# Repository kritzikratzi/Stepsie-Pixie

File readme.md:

<font color="red">WIP, please come back in a few weeks/months</font>

# Stepsie Pixie (WIP!)

This is a small project that combines: 

* stepper motor (to move your camera)
* relais (to trigger virtually any SLR camera)
* display+buttons (to adjust a few settings in place)
* esp8266 (as a controller, if things go well it'll also offer a web-ui)

The repository contains the code for the Arduino IDE and (soon) the eagle layout for making the board.

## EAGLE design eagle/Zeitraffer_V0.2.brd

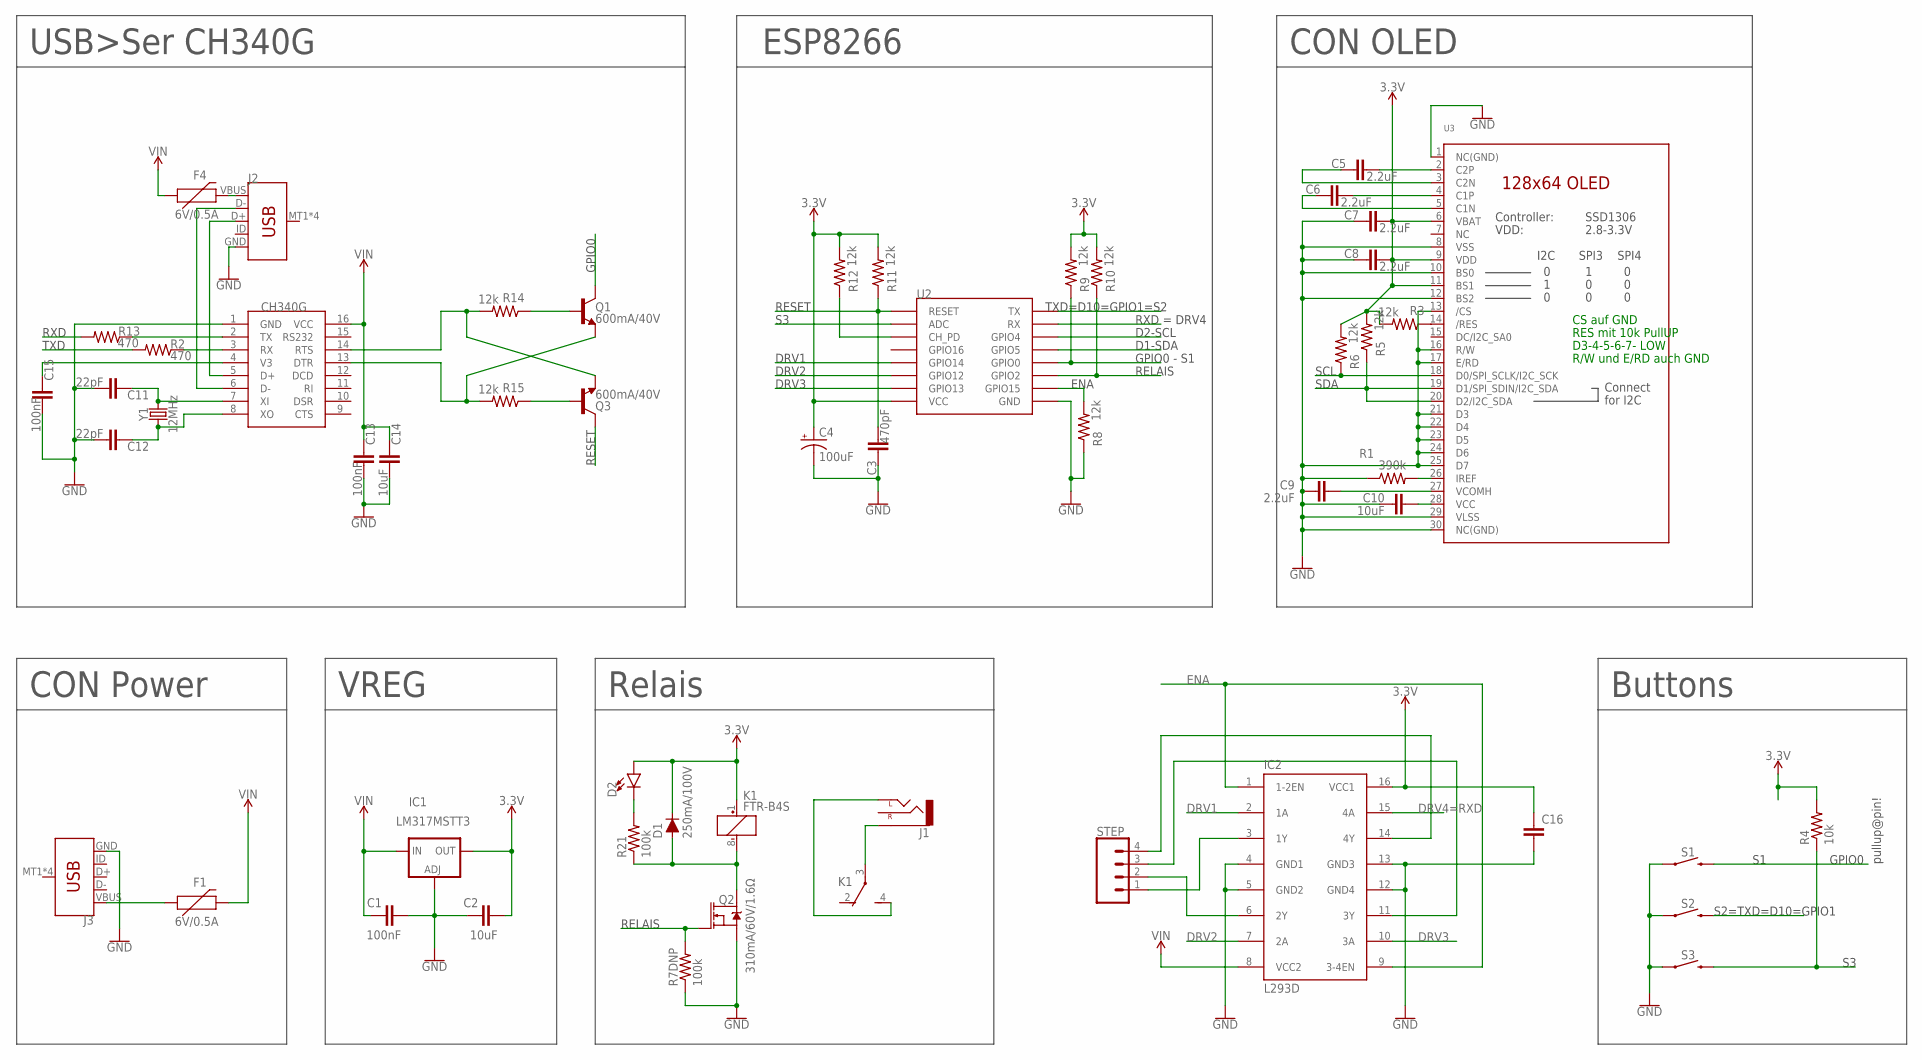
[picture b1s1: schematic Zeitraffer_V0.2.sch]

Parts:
C1, C13, C15: 100nF; 0805
C2, C10, C14: 10uF; 0805
C3: 470pF; 0805
C4: 100uF; EIA7343
C5, C6, C7, C8, C9: 2.2uF; 0805
C11, C12: 22pF; 0805
C16: C-EUC0805; C0805
D1: 250mA/100V; SOD-323
D2: LED1206-BOTTOM; LED-1206-BOTTOM
F1, F4: 6V/0.5A; 1206
IC1: LM317MSTT3; SOT223
IC2: L293D; DIL16
J1: AUDIO_JACK_2.5MM_2.5MM; STEREOJACK2.5MM_STEREOJACK2.5MM
J2, J3: USB_MICRO-B_SMT; USB-MICROB
K1: FTR-B4S
Q1, Q3: 600mA/40V; SOT23-3
Q2: 310mA/60V/1.6Ω; SOT323
R1: 390k; 0805
R2, R13: 470; 0603
R3, R5, R6, R8, R9, R10, R11, R12, R14, R15: 12k; R0805
R4: 10k; R0805
R7DNP, R21: 100k; R0805
S1, S2, S3: MOMENTARY-SWITCH-SPST-PTH-6.0MM; TACTILE_SWITCH_PTH_6.0MM
STEP: CONN_04JST-PTH; JST-4-PTH
U2: ESP12SMD; ESP12-SMD
U3: DISP_OLED_UG-2864HSWEG01; UG-2864HSWEG01_1.3_WRAPAROUND
U$2: CH340G; SOIC16
Y1: 12MHz; CRYSTAL-SMD-5X3.2-4PAD

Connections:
3.3V: C2.2, C4.A (+), C7.2, C8.2, C16.1, D1.C, D2.A, IC1.4 (OUT), IC2.16 (VCC1), K1.1 (+), R3.2, R4.2, R5.2, R6.2, R9.2, R10.2, R11.2, R12.2, U2.VCC, U3.6 (VBAT), U3.9 (VDD), U3.11 (BS1)
DRV1: IC2.2 (1A), U2.GPIO14
DRV2: IC2.7 (2A), U2.GPIO12
DRV3: IC2.10 (3A), U2.GPIO13
ENA: IC2.1 (1-2EN), IC2.9 (3-4EN), R8.2, U2.GPIO15
GND: C1.2, C2.1, C3.1, C4.C (-), C7.1, C8.1, C9.1, C10.1, C11.2, C12.2, C13.2, C14.2, C15.2, C16.2, IC1.1 (ADJ), IC2.4 (GND1), IC2.5 (GND2), IC2.12 (GND4), IC2.13 (GND3), J2.GND, J3.GND, Q2.2 (S), R1.1, R7DNP.1, R8.1, S1.1, S2.1, S3.1, U2.GND, U3.1 (NC(GND)), U3.8 (VSS), U3.10 (BS0), U3.12 (BS2), U3.13 (/CS), U3.16 (R/W), U3.17 (E/RD), U3.21 (D3), U3.22 (D4), U3.23 (D5), U3.24 (D6), U3.25 (D7), U3.29 (VLSS), U3.30 (NC(GND)), U$2.1 (GND)
GPIO0: Q1.3 (C), R9.1, S1.3 (2), U2.GPIO0
unnamed: F1.1, J3.VBUS
unnamed: J1.RING1 (SLEEVE), K1.3
unnamed: D1.A, K1.8 (-), Q2.3 (D), R21.1
unnamed: J1.SHIELD (LEFT), K1.4 (S)
unnamed: C5.2, U3.2 (C2P)
unnamed: C6.2, U3.4 (C1P)
unnamed: C5.1, U3.3 (C2N)
unnamed: C6.1, U3.5 (C1N)
unnamed: R1.2, U3.26 (IREF)
unnamed: C9.2, U3.27 (VCOMH)
unnamed: C10.2, U3.28 (VCC)
unnamed: R3.1, U3.14 (/RES)
unnamed: C11.1, U$2.7 (XI), Y1.3 (2)
unnamed: R12.1, U2.CH_PD
unnamed: C12.1, U$2.8 (XO), Y1.1
unnamed: J2.D+, U$2.5 (D+)
unnamed: J2.D-, U$2.6 (D-)
unnamed: Q3.2 (E), R14.2, U$2.14 (RTS)
unnamed: Q1.2 (E), R15.2, U$2.13 (DTR)
unnamed: R13.1, U$2.2 (TX)
unnamed: R2.1, U$2.3 (RX)
unnamed: C15.1, U$2.4 (V3)
unnamed: Q3.1 (B), R15.1
unnamed: Q1.1 (B), R14.1
unnamed: IC2.3 (1Y), STEP.1
unnamed: IC2.6 (2Y), STEP.2
unnamed: F4.2, J2.VBUS
unnamed: D2.C, R21.2
unnamed: IC2.14 (4Y), STEP.4
unnamed: IC2.11 (3Y), STEP.3
RELAIS: Q2.1 (G), R7DNP.2, R10.1, U2.GPIO2
RESET: C3.2, Q3.3 (C), R11.1, U2.RESET
RXD: IC2.15 (4A), R13.2, U2.RXD0 (RX)
S3: R4.1, S3.3 (2), U2.ADC
SCL: R6.1, U2.GPIO4, U3.18 (D0/SPI_SCLK/I2C_SCK)
SDA: R5.1, U2.GPIO5, U3.19 (D1/SPI_SDIN/I2C_SDA), U3.20 (D2/I2C_SDA)
TXD: R2.2, S2.3 (2), U2.TXD0 (TX)
VIN: C1.1, C13.1, C14.1, F1.2, F4.1, IC1.3 (IN), IC2.8 (VCC2), U$2.16 (VCC)

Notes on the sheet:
SCL
SDA
CON OLED
VREG
S2=TXD=D10=GPIO1
Buttons
CON Power
RELAIS
Relais
TXD=D10=GPIO1=S2
RXD = DRV4
GPIO0 - S1
RESET
D1-SDA
D2-SCL
GPIO0
pullup@pin!
DRV2
DRV3
DRV1
ESP8266
TXD
RXD
USB>Ser CH340G
ENA
DRV4=RXD
CS auf GND
RES mit 10k PullUP
D3-4-5-6-7- LOW
R/W und E/RD auch GND

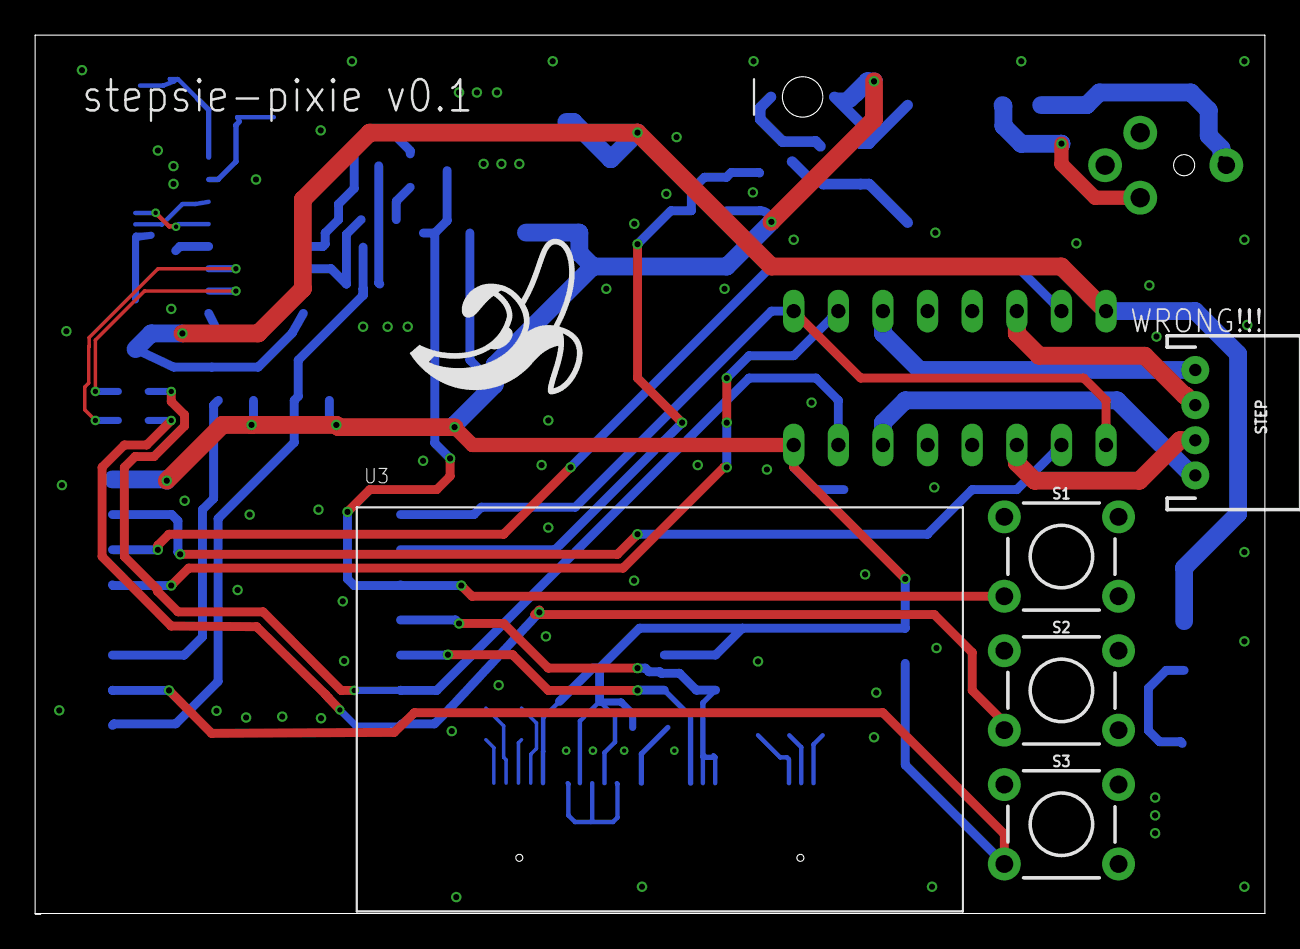
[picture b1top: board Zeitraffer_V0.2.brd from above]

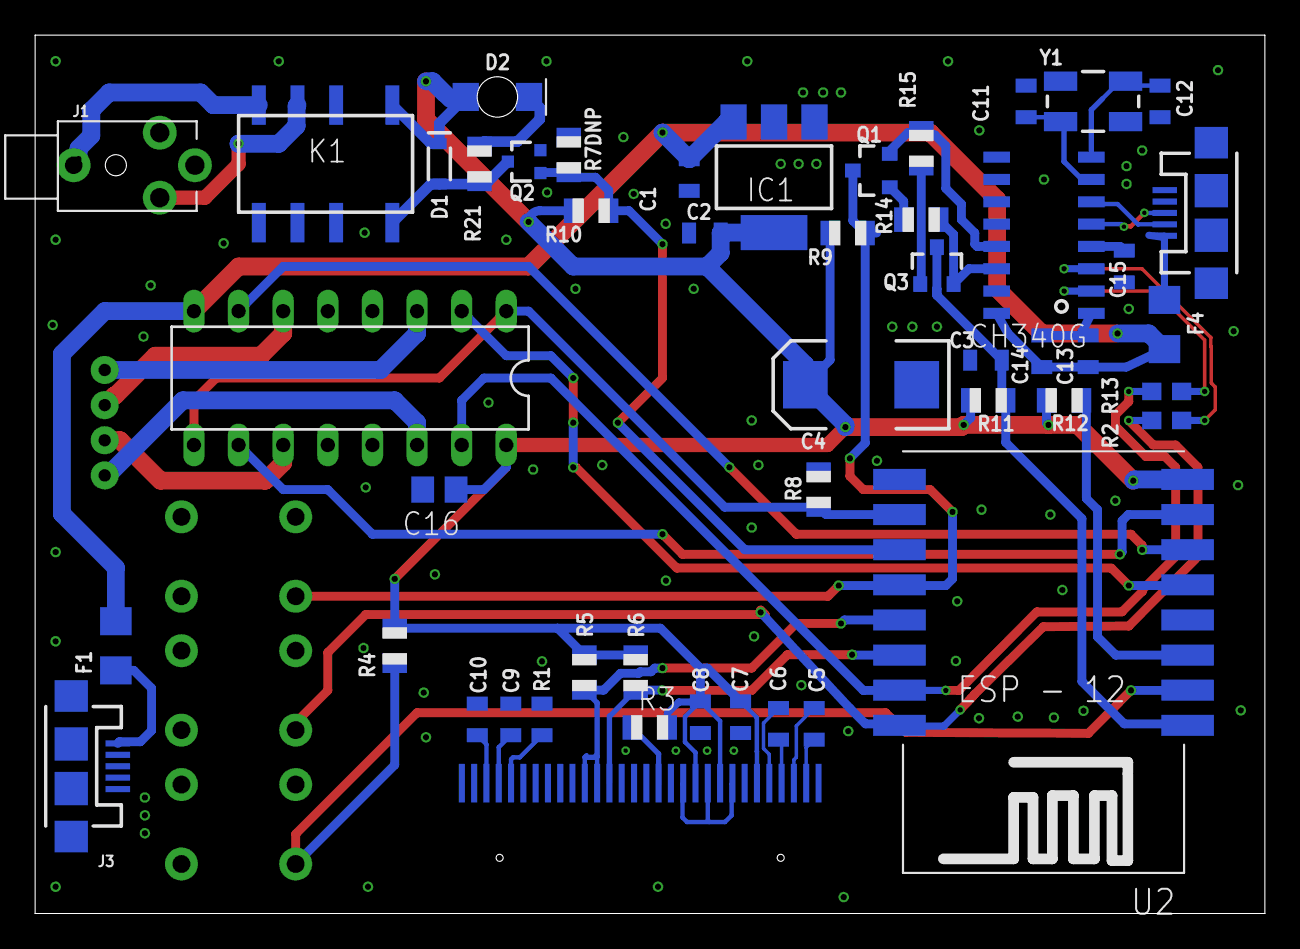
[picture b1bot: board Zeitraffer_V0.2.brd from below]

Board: 2 copper layers, 70.0 x 50.0 mm, 53 parts (48 on the bottom side), 45 nets.

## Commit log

2018-02-25 added eagle files
2018-02-25 removed unnecessary adafruit files
2018-02-26 banana
2018-02-26 final touchups generated gerber
2018-11-30 added 3d models
2018-12-16 arduino: updated pins so it matches the eagle layout, added icons for +/-/next, disable motor while inactive
2018-12-16 added new board version

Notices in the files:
parts and their libraries:
SparkFun-Capacitors: Licensing: Creative Commons ShareAlike 4.0 International - https://creativecommons.org/licenses/by-sa/4.0
